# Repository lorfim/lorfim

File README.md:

- 👋 Hi, I’m @lorfim
- 👀 I’m interested in RF and analog electronics
- 🌱 I’m currently learning how to use kicad and python

<!---
lorfim/lorfim is a ✨ special ✨ repository because its `README.md` (this file) appears on your GitHub profile.
You can click the Preview link to take a look at your changes.
--->

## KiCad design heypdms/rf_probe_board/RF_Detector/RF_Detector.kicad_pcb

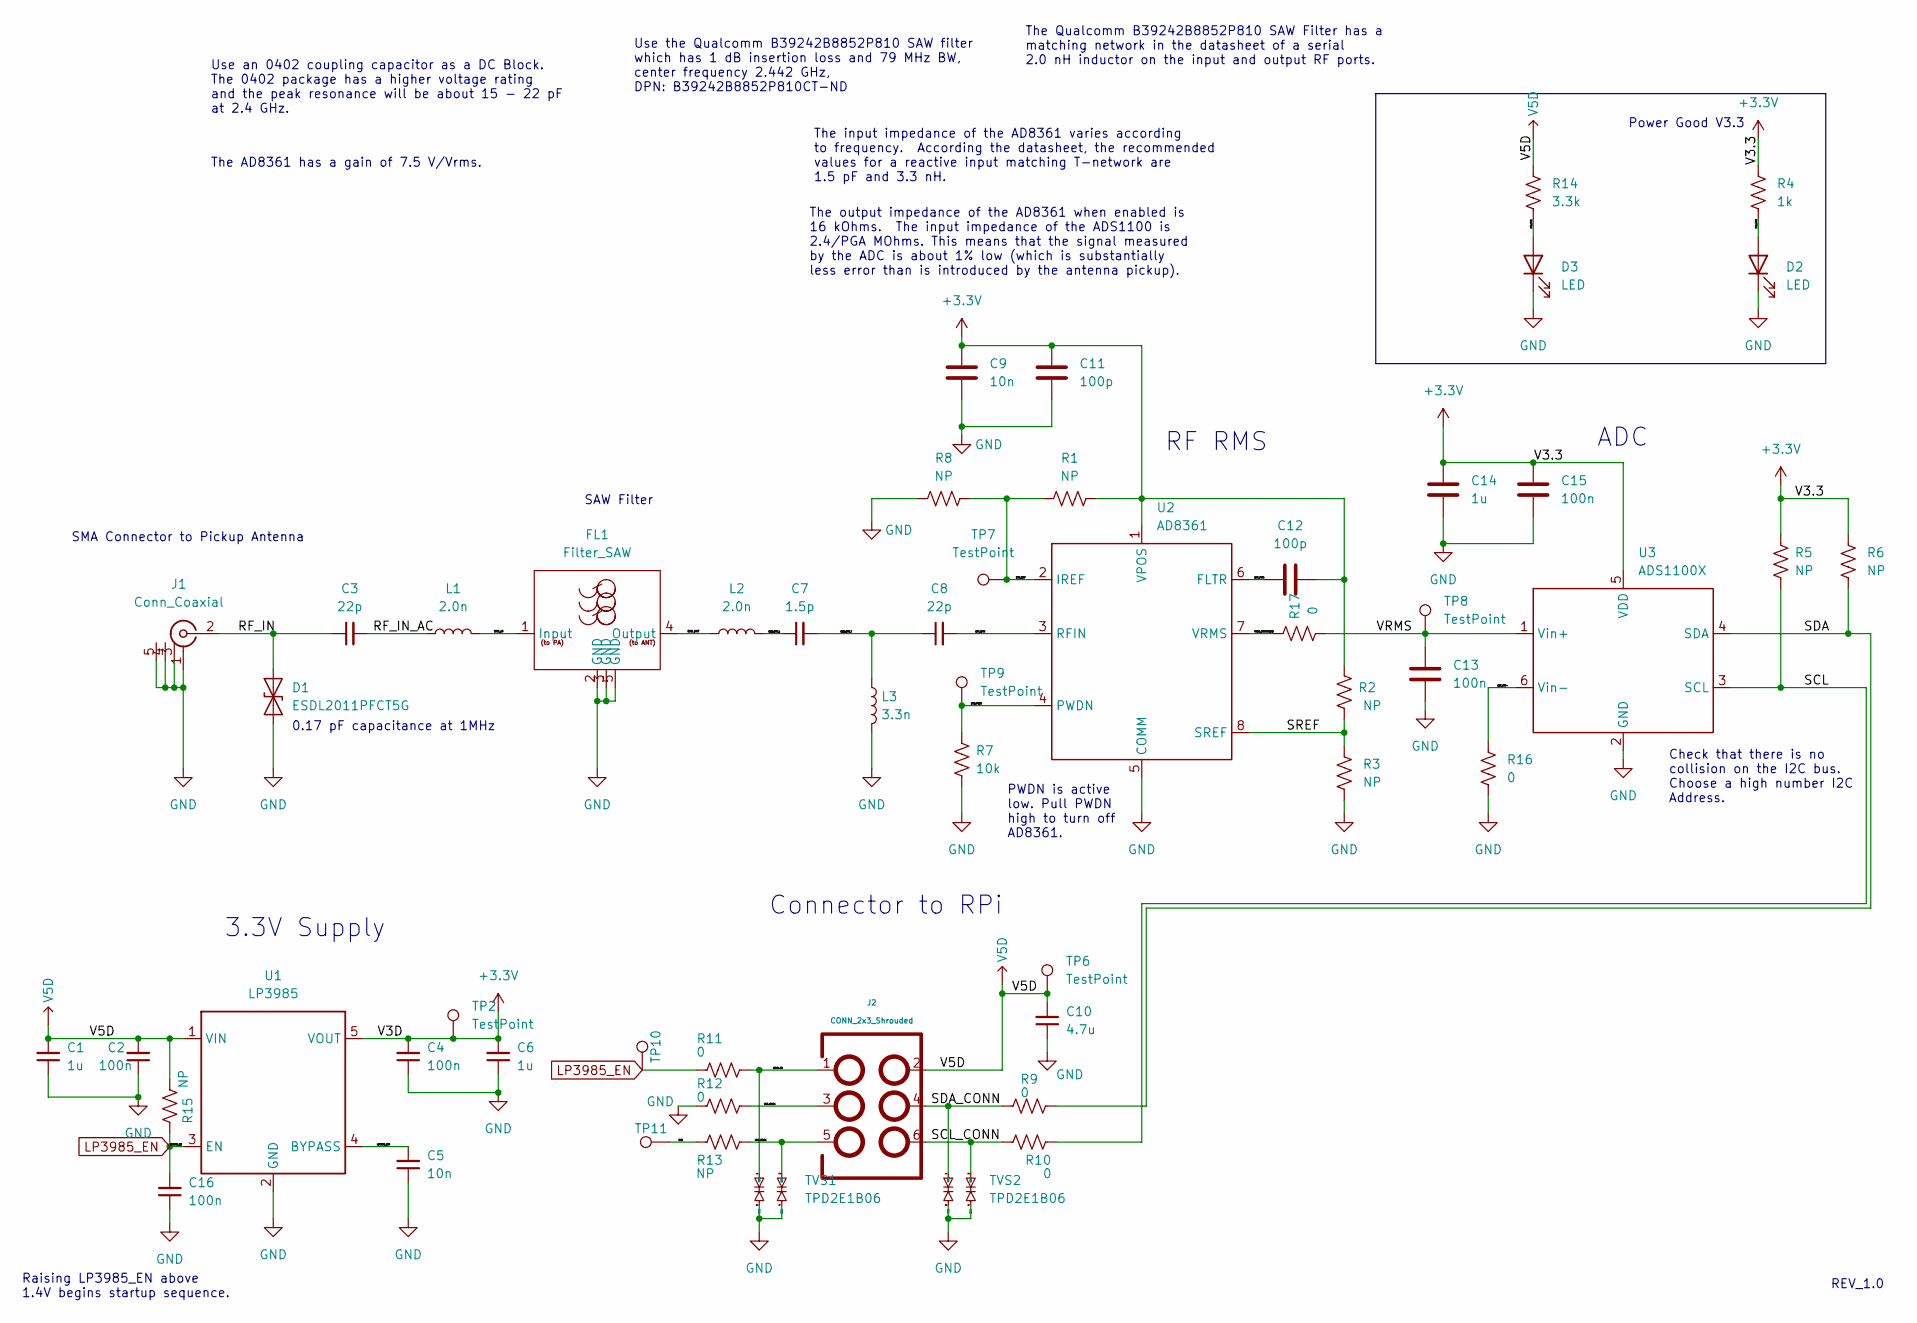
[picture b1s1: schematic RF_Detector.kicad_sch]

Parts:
C1, C6, C14: 1u; C_0402_1005Metric
C2, C4, C13, C15, C16: 100n; C_0402_1005Metric
C3, C8: 22p; C_0402_1005Metric
C5, C9: 10n; C_0402_1005Metric
C7: 1.5p; C_0201_0603Metric
C10: 4.7u; C_1206_3216Metric
C11, C12: 100p; C_0402_1005Metric
D1: ESDL2011PFCT5G; C_0201_0603Metric
D2, D3: LED; D_0603_1608Metric
FL1: Filter_SAW; 5-SMD
J1: Conn_Coaxial; conn_sma_endlaunch_female_062
J2: CONN_2x3_Shrouded; CONN_2x3_2mm_shrouded_TH
L1, L2: 2.0n; L_0402_1005Metric
L3: 3.3n; L_0402_1005Metric
R1, R2, R3, R5, R6, R8, R13, R15: NP; R_0402_1005Metric
R4: 1k; R_0402_1005Metric
R7: 10k; R_0402_1005Metric
R9, R10, R11, R16, R17: 0; R_0402_1005Metric
R12: 0; R_0603_1608Metric
R14: 3.3k; R_0402_1005Metric
TP2, TP6, TP7, TP8, TP9, TP10, TP11: TestPoint; testpoint_1.0mm
TVS1, TVS2: TPD2E1B06; SOT-23-6
U1: LP3985; SOT-23-5
U2: AD8361; 8-MSOP
U3: ADS1100X; SOT-23-6
V5D1, V5D3: V5D
V5D2: (no value)

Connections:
+3V3: C4.2, C6.2, C9.1, C11.1, C12.2, C14.1, C15.1, R1.2, R2.2, R4.1, R5.1, R6.1, TP2.1, U1.5 (VOUT), U2.1 (VPOS), U3.5 (VDD)
/ADC_VIN-: R16.2, U3.6 (Vin-)
/CHK: R13.1, TP11.1
/CHK_CONN: J2.5, R13.2, TVS1.2 (IOB1)
/CONN_EN: J2.1, R11.2, TVS1.1 (IOA1)
/DET_FLTR: C12.1, U2.6 (FLTR)
/DET_IREF: R1.1, R8.2, TP7.1, U2.2 (IREF)
/DET_PWDN: R7.1, TP9.1, U2.4 (PWDN)
/DET_RFIN: C8.2, U2.3 (RFIN)
/GND_CONN: J2.3, R12.2
/LED_3V3: D2.2 (A), R4.2
/LED_V5D: D3.2 (A), R14.2
/LP3985_BYP: C5.2, U1.4 (BYPASS)
/RF_IN: C3.1, D1.2 (A2), J1.2 (In)
/RF_IN_AC: C3.2, L1.1
/SAW_IN: FL1.1 (Input), L1.2
/SAW_OUT: FL1.4 (Output), L2.1
/SAW_OUT_L: C7.1, L2.2
/SAW_OUT_T: C7.2, C8.1, L3.1
/SCL: R5.2, R10.2, U3.3 (SCL)
/SCL_CONN: J2.6, R10.1, TVS2.2 (IOB1)
/SDA: R6.2, R9.2, U3.4 (SDA)
/SDA_CONN: J2.4, R9.1, TVS2.1 (IOA1)
/SREF: R2.1, R3.2, U2.8 (SREF)
/V5D: C1.2, C2.2, C10.2, J2.2, R14.1, R15.2, TP6.1, U1.1 (VIN), V5D1., V5D2., V5D3.
/VRMS: C13.1, R17.1, TP8.1, U3.1 (Vin+)
/VRMS_UNFILTERED: R17.2, U2.7 (VRMS)
GND: C1.1, C2.1, C4.1, C5.1, C6.1, C9.2, C10.1, C11.2, C13.2, C14.2, C15.2, C16.1, D1.1 (A1), D2.1 (K), D3.1 (K), FL1.2 (GND), FL1.3 (GND), FL1.5 (GND), J1.1 (GND), J1.3 (GND), J1.4 (GND), J1.5 (GND), L3.2, R3.1, R7.2, R8.1, R12.1, R16.1, TVS1.4 (IOB2), TVS1.5 (IOE2), TVS2.4 (IOB2), TVS2.5 (IOE2), U1.2 (GND), U2.5 (COMM), U3.2 (GND); also elsewhere on the board
LP3985_EN: C16.2, R11.1, R15.1, TP10.1, U1.3 (EN)

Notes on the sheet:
0.17 pF capacitance at 1MHz
The input impedance of the AD8361 varies according to frequency. According the datasheet, the recommended values for a reactive input matching T-network are 1.5 pF and 3.3 nH.
Power Good V3.3
The Qualcomm B39242B8852P810 SAW Filter has a matching network in the datasheet of a serial 2.0 nH inductor on the input and output RF ports.
Connector to RPi
The AD8361 has a gain of 7.5 V/Vrms.
The output impedance of the AD8361 when enabled is 16 kOhms. The input impedance of the ADS1100 is 2.4/PGA MOhms. This means that the signal measured by the ADC is about 1% low (which is substantially less error than is introduced by the antenna pickup).
PWDN is active low. Pull PWDN high to turn off AD8361.
SAW Filter
Use an 0402 coupling capacitor as a DC Block. The 0402 package has a higher voltage rating and the peak resonance will be about 15 - 22 pF at 2.4 GHz.
RF RMS
Use the Qualcomm B39242B8852P810 SAW filter which has 1 dB insertion loss and 79 MHz BW, center frequency 2.442 GHz, DPN: B39242B8852P810CT-ND
SMA Connector to Pickup Antenna
ADC
Raising LP3985_EN above 1.4V begins startup sequence.
Check that there is no collision on the I2C bus. Choose a high number I2C Address.
REV_1.0
3.3V Supply

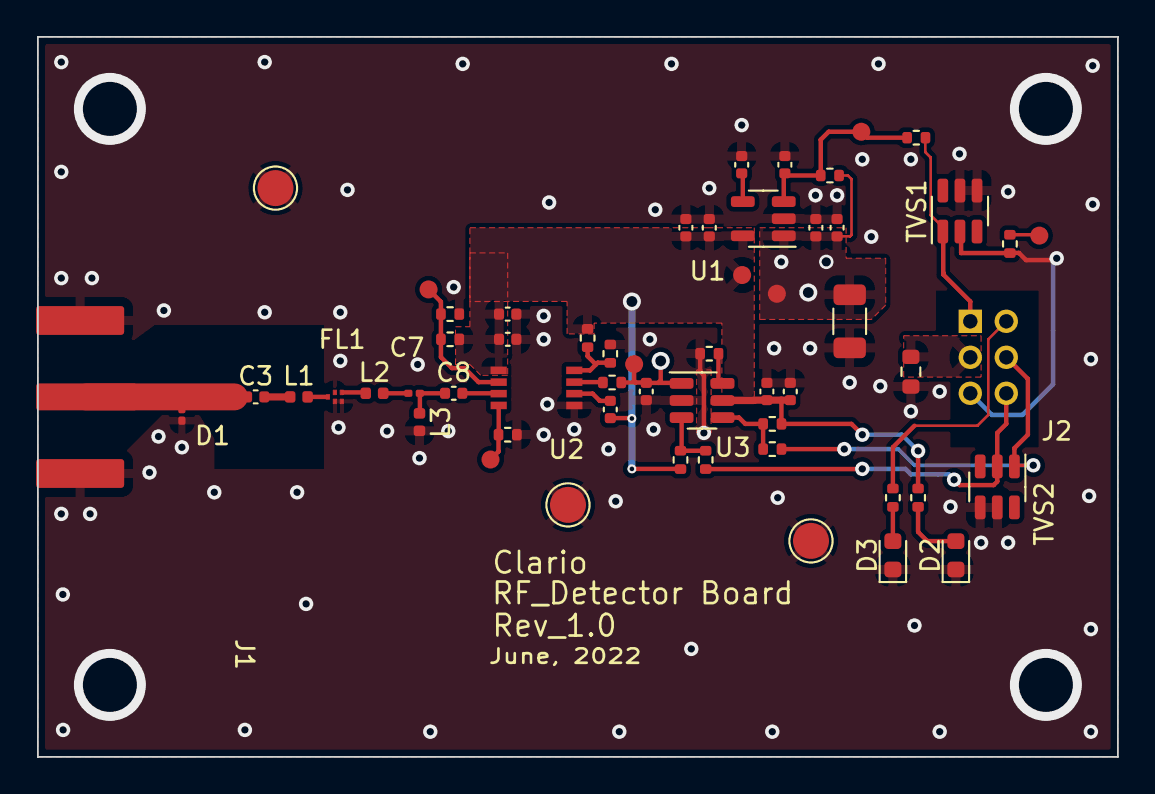
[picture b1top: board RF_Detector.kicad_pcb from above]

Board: 2 copper layers, 60.0 x 40.0 mm, 57 parts (0 on the bottom side), 29 nets.

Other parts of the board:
TP3, TP4, TP5: TestPoint; TestPoint_Pad_D2.0mm

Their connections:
GND: TP3.1, TP4.1, TP5.1; also elsewhere on the board

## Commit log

2022-05-27 rf_detector kicad files
2022-06-01 Needs the 2x3 connector to be a 2mm pitch. The pcb is started.
2022-06-06 RF_Detector kicad board schematic completed with no bad ERCs and board is routed but needs a DRC
2022-06-07 RF_Detector board with zero airwires and most of the silkscreen
